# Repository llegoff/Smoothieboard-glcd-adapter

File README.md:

Smoothieboard-glcd-adapter
==========================

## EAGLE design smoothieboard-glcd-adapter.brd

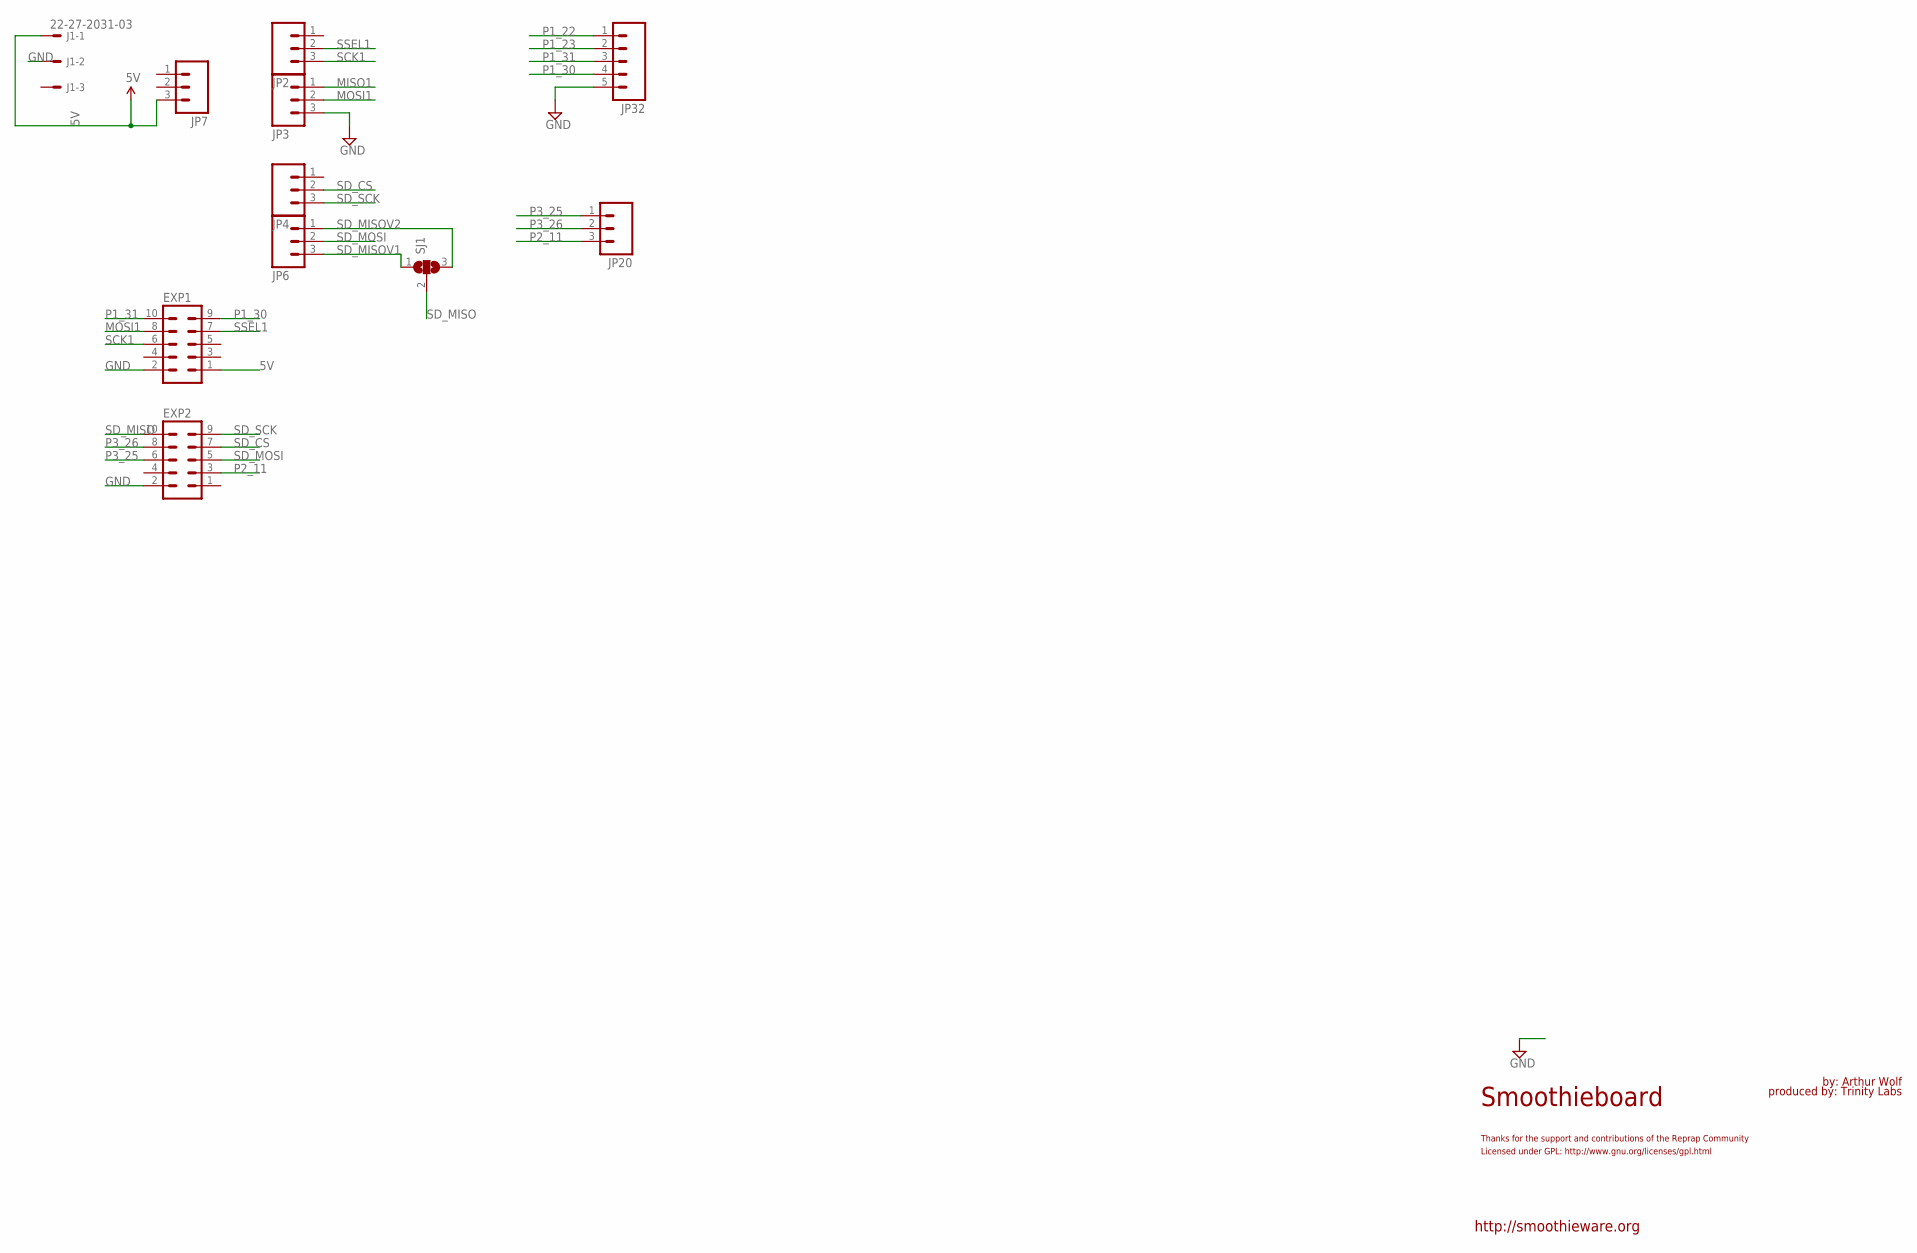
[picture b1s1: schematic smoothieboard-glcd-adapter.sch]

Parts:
EXP1, EXP2: ML10
J1: 22-27-2031-03; 6410-03
JP2, JP3, JP4, JP6: M031X03_NO_SILK; 1X03_NO_SILK
JP7, JP20: M03PTH; 1X03
JP32: M05PTH; 1X05
SJ1: SJ2W; SJ_2

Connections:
5V: EXP1.1, J1.1, JP7.3
GND: EXP1.2, EXP2.2, J1.2, JP3.3, JP32.5
MISO1: JP3.1
MOSI1: EXP1.8, JP3.2
P1_22: JP32.1
P1_23: JP32.2
P1_30: EXP1.9, JP32.4
P1_31: EXP1.10, JP32.3
P2_11: EXP2.3, JP20.3
P3_25: EXP2.6, JP20.1
P3_26: EXP2.8, JP20.2
SCK1: EXP1.6, JP2.3
SD_CS: EXP2.7, JP4.2
SD_MISO: EXP2.10, SJ1.2
SD_MISOV1: JP6.3, SJ1.1
SD_MISOV2: JP6.1, SJ1.3
SD_MOSI: EXP2.5, JP6.2
SD_SCK: EXP2.9, JP4.3
SSEL1: EXP1.7, JP2.2

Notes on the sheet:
http://smoothieware.org
Smoothieboard
by: Arthur Wolf
produced by: Trinity Labs
Licensed under GPL: http://www.gnu.org/licenses/gpl.html
Thanks for the support and contributions of the Reprap Community

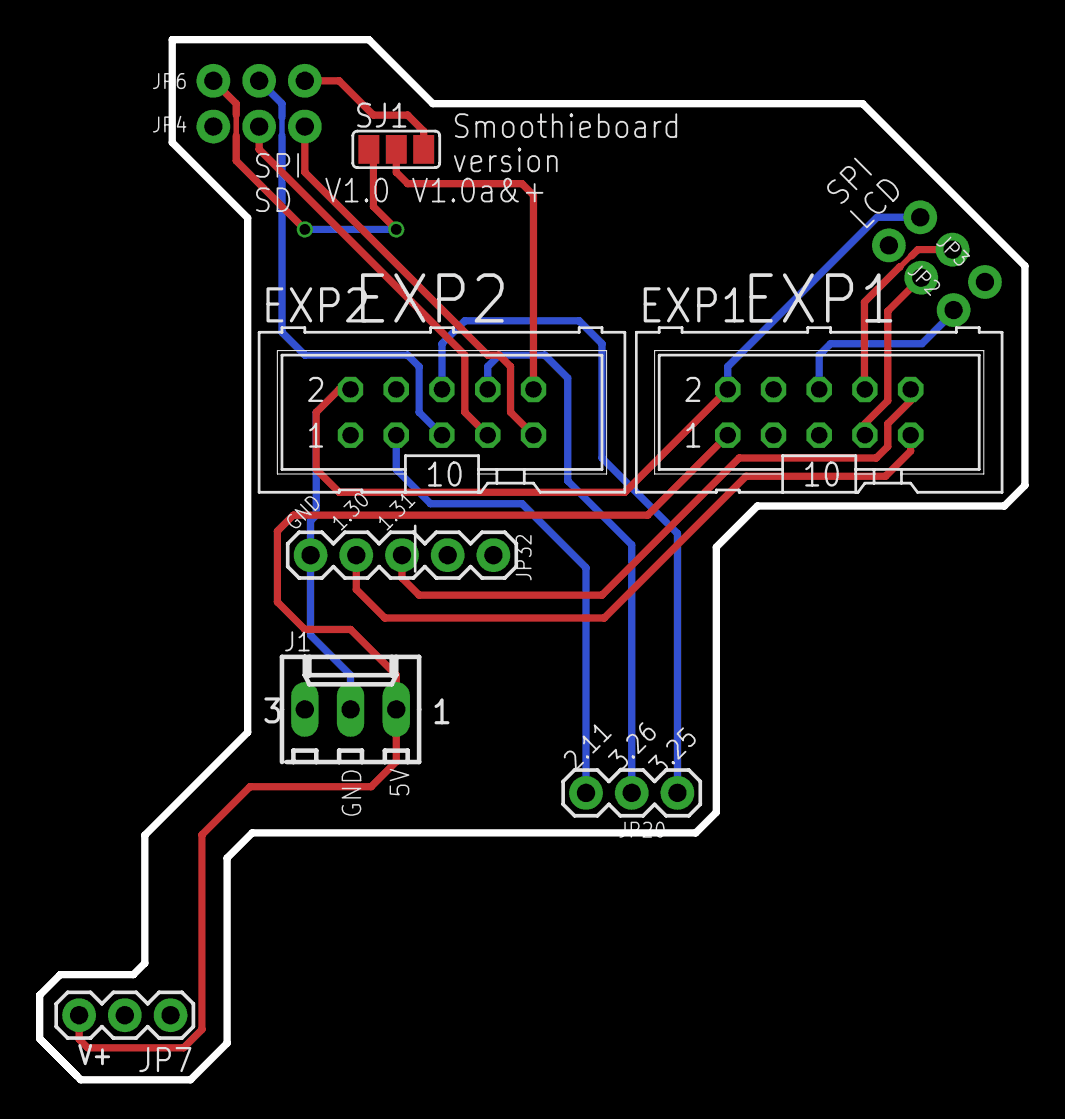
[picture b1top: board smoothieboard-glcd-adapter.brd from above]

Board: 2 copper layers, 54.7 x 57.8 mm, 11 parts (0 on the bottom side), 16 nets.

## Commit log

2014-07-10 pcb.png
